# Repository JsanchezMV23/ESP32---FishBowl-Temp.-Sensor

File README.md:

# ESP32 - FishBowl Temperature Sensor

**ESP32 based Temperature Sensor for a Fishbowl from scratch**. This small device tracks the Temperature of a small fish tank using a *DS18B20 Temperature Sensor* and displays its readings in both a *Web Server* and a *RC16202A 16x2 LCD display*.

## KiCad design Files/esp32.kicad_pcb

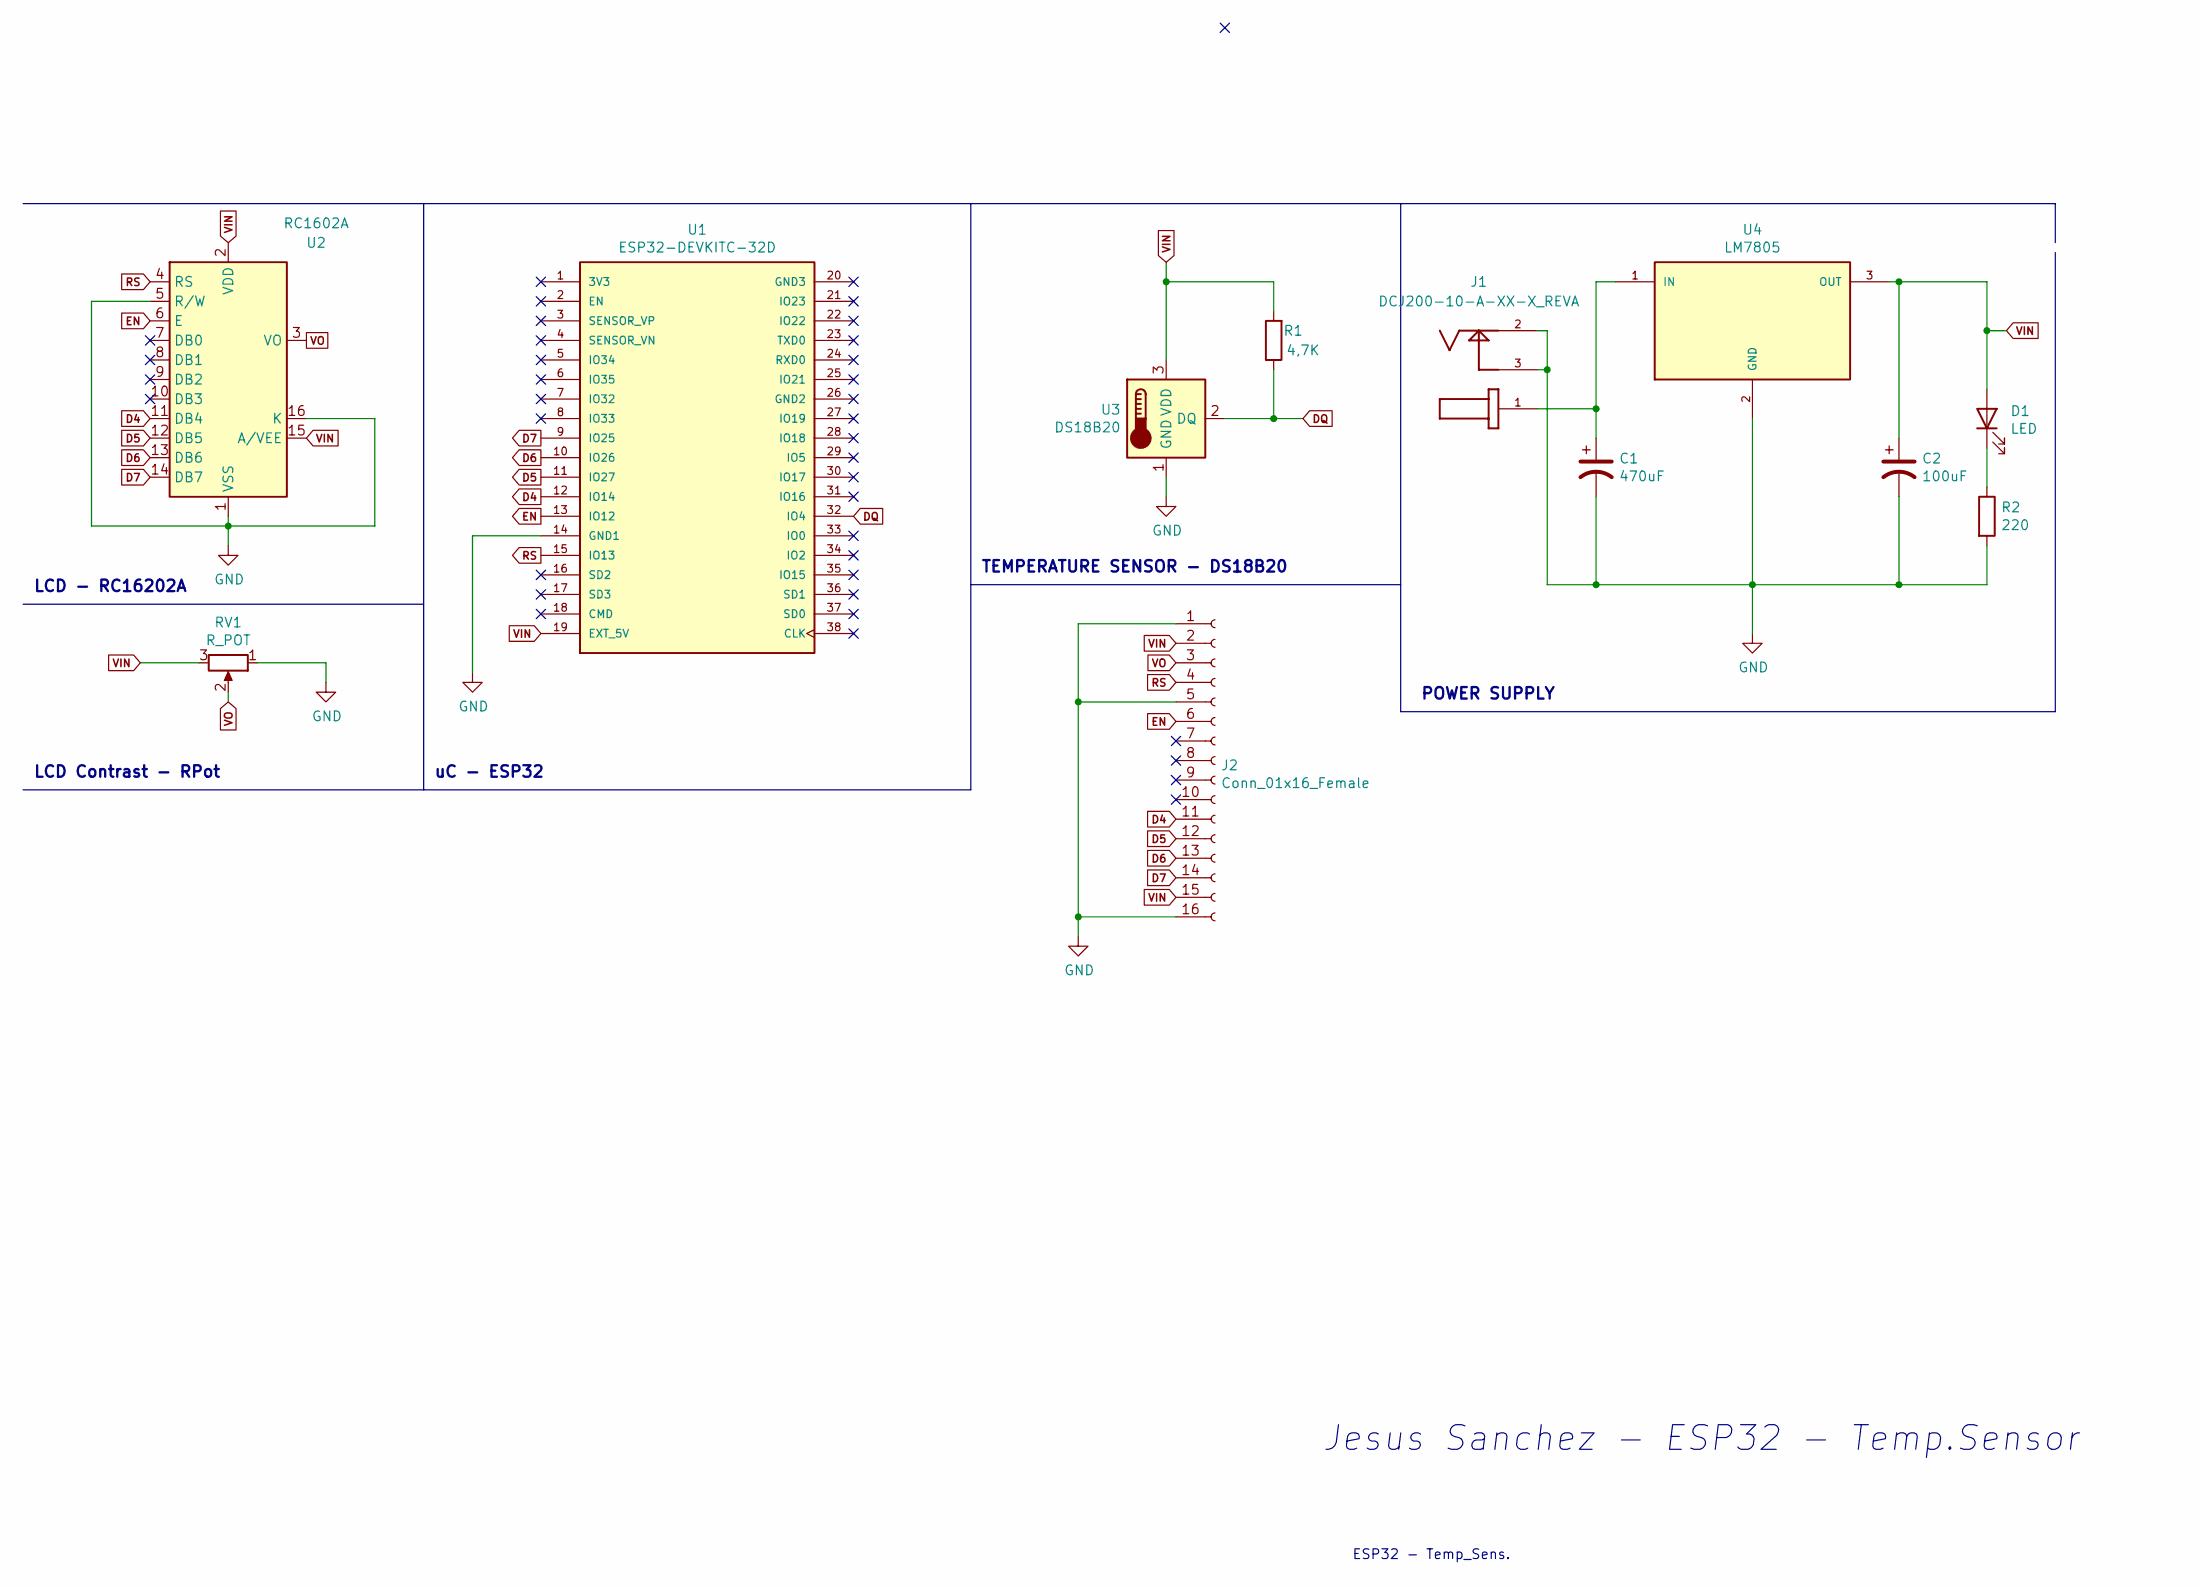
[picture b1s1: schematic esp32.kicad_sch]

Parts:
C1: 470uF; CP_Radial_D10.0mm_P5.00mm
C2: 100uF; CP_Radial_D10.0mm_P5.00mm
D1: LED; LED_D5.0mm
J1: DCJ200-10-A-XX-X_REVA; GCT_DCJ200-10-A-XX-X_REVA
J2: Conn_01x16_Female; PinSocket_1x16_P2.54mm_Vertical
R1: 4,7K; R_Axial_DIN0207_L6.3mm_D2.5mm_P10.16mm_Horizontal
R2: 220; R_Axial_DIN0207_L6.3mm_D2.5mm_P10.16mm_Horizontal
RV1: R_POT; Potentiometer_Piher_PT-6-V_Vertical
U1: ESP32-DEVKITC-32D; MODULE_ESP32-DEVKITC-32D; PARTREV 4
U2: RC1602A
U3: DS18B20; TO-92_Inline
U4: LM7805; TO220

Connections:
D4: J2.11, U1.12 (IO14), U2.11 (DB4)
D5: J2.12, U1.11 (IO27), U2.12 (DB5)
D6: J2.13, U1.10 (IO26), U2.13 (DB6)
D7: J2.14, U1.9 (IO25), U2.14 (DB7)
DQ: R1.1, U1.32 (IO4), U3.2 (DQ)
EN: J2.6, U1.13 (IO12), U2.6 (E)
GND: C1.2, C2.2, J1.2, J1.3, J2.1, J2.5, J2.16, R2.2, RV1.1, U1.14 (GND1), U2.1 (VSS), U2.5 (R/W), U2.16 (K), U3.1 (GND), U4.2 (GND)
unnamed: C1.1, J1.1, U4.1 (IN)
unnamed: D1.1 (K), R2.1
RS: J2.4, U1.15 (IO13), U2.4 (RS)
VIN: C2.1, D1.2 (A), J2.2, J2.15, R1.2, RV1.3, U1.19 (EXT_5V), U2.2 (VDD), U2.15 (A/VEE), U3.3 (VDD), U4.3 (OUT)
VO: J2.3, RV1.2, U2.3 (VO)

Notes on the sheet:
uC - ESP32
LCD - RC16202A
POWER SUPPLY
Jesus Sanchez - ESP32 - Temp.Sensor
TEMPERATURE SENSOR - DS18B20
ESP32 - Temp_Sens.
LCD Contrast - RPot

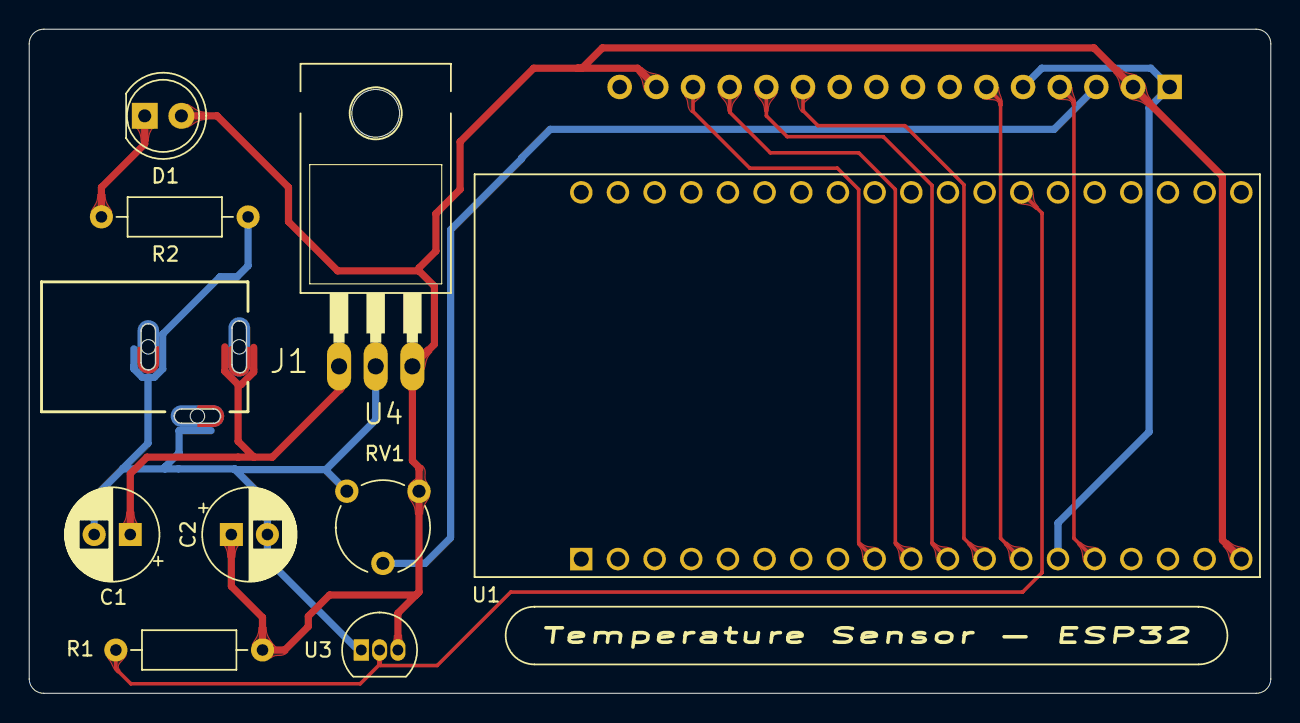
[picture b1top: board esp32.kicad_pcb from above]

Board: 2 copper layers, 86.0 x 46.0 mm, 11 parts (1 on the bottom side), 12 nets.

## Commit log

2022-01-03 Create Images
2022-01-04 Create a
2022-01-04 Create b
